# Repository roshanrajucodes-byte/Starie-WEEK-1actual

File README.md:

# Starie-WEEK-1actual
What i made this week

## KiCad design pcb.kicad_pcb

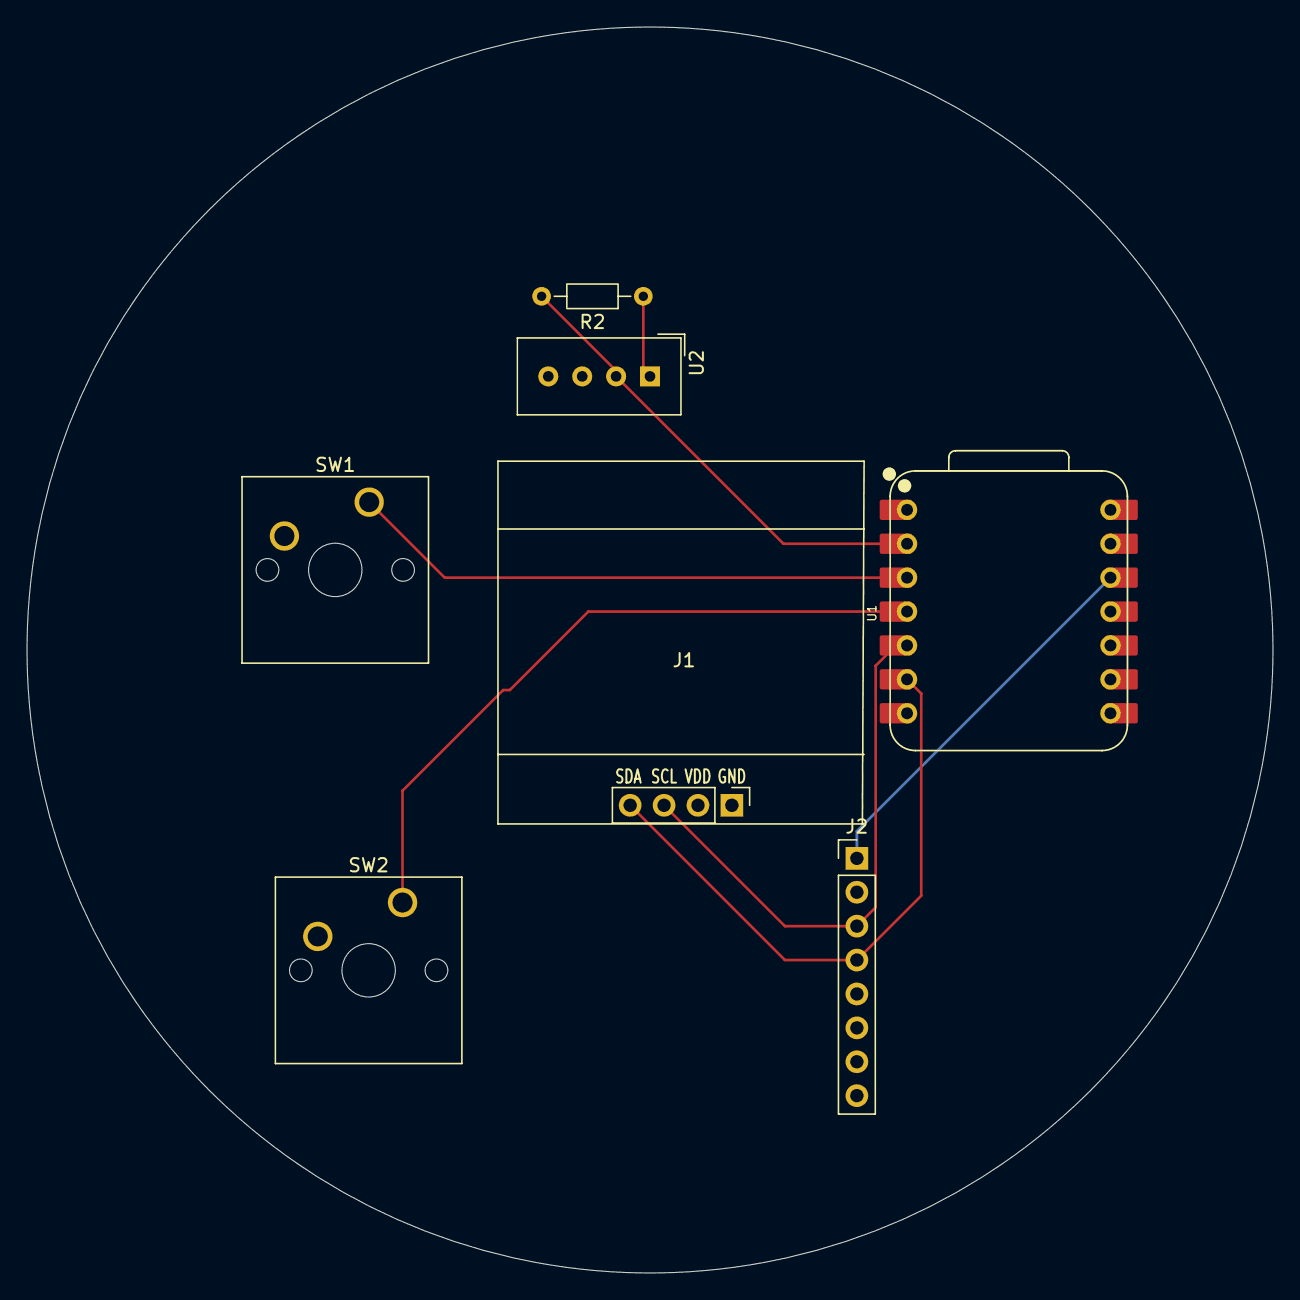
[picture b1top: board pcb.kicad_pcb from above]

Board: 2 copper layers, 93.3 x 93.3 mm, 7 parts (0 on the bottom side), 7 nets.

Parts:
J1: Conn_01x04_Pin; Display_128x64_096_I2C
J2: Conn_01x08_Pin; PinHeader_1x08_P2.54mm_Vertical
R2: 10k; R_Axial_DIN0204_L3.6mm_D1.6mm_P7.62mm_Horizontal
SW1, SW2: SW_Push_Dual_x2; SW_Cherry_MX_1.00u_PCB
U1: XIAO-ESP32-C3-SMD; XIAO-ESP32-C6-DIP
U2: DHT11; Aosong_DHT11_5.5x12.0_P2.54mm

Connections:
+3.3V: J1.2, J2.1, R2.1, U1.12 (3V3_OUT), U2.1 (VDD)
/DHT11 DATA: R2.2, U1.2 (D1), U2.2 (DATA)
/GP102: SW1.1 (C), U1.3 (D2)
/GP103: SW2.1 (C), U1.4 (D3)
/SCL: J1.3, J2.3, U1.5 (D4)
/SDA: J1.4, J2.4, U1.6 (D5)
GND: J1.1, J2.2, SW1.2 (D), SW2.2 (D), U1.13 (GND), U2.4 (GND)
